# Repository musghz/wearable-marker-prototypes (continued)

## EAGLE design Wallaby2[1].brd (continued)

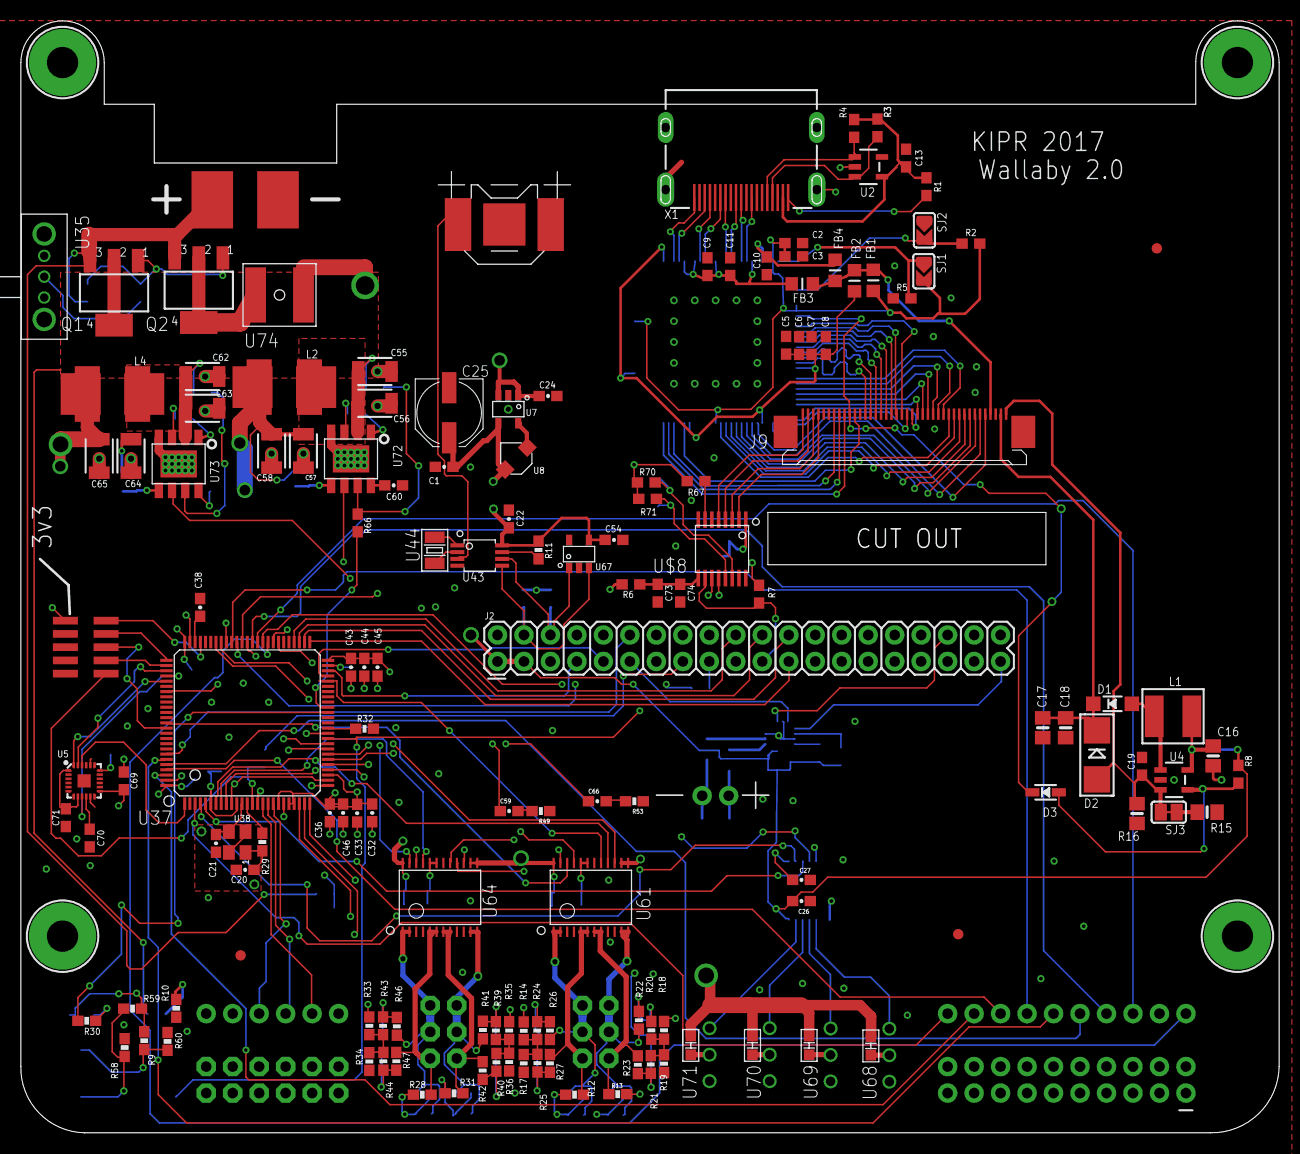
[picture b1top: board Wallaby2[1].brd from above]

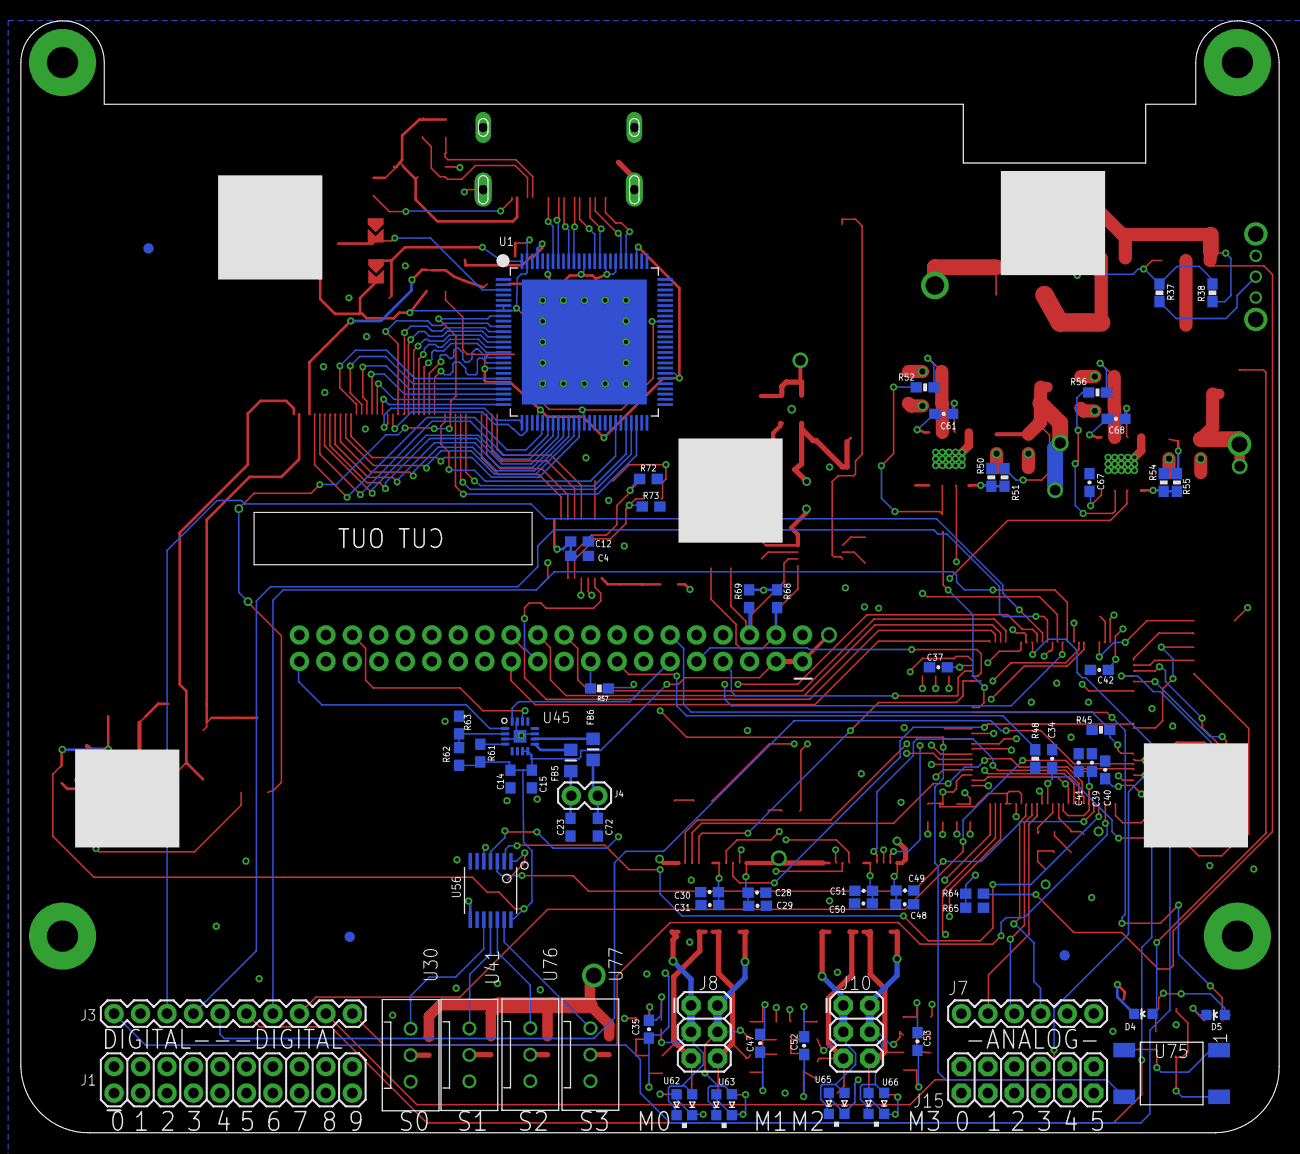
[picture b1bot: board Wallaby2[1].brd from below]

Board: 6 copper layers, 120.7 x 106.7 mm, 222 parts (73 on the bottom side), 199 nets.

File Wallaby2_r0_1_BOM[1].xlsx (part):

Item # | Qty | Ref Des | Manufacturer | Mfg Part # | Dist Part # | Distributor | Description | Package | Type
1 | 1 | J4 |  |  |  |  | Holes for speaker wire | 1X02 | DNS
2 | 1 | J3 | Harwin | M20-7821042 | 855-M20-7821042 | mouser | 1x10 female header | J3 | Thru-hole
3 | 1 | J1 | Harwin | M20-7831046 | 855-M20-7831046 | mouser | 2x10 female header | 2X10 | Thru-hole
4 | 1 | J7 | Harwin | M20-7820642 | 855-M20-7820642 | mouser | 1x6 female header | 1X06 | Thru-hole
5 | 2 | SJ1, SJ2 |  |  |  |  |  | SOLDERJUMPER_ARROW_NOPASTE | DNS
6 | 1 | U35 | C&K | 0S102011MA1QN1 | 611-OS102011MA1QN1 | mouser |  | OS-SPDT-MINI-SLIDE_SWITCH | Thru-hole
7 | 1 | SJ3 |  |  |  |  | -25mA | SOLDERJUMPER_CLOSEDWIRE | DNS
8 | 6 | R48,R66, R70, R71, R72, R73 | Yageo | RC0603JR-070RL | 603-RC0603JR-070RL | mouser | 0 ohm 0603 | 0603 | smt
8 | 2 | R6, R67 | Yageo | RC0603JR-070RL | 603-RC0603JR-070RL | mouser | 0 ohm 0603 | 0603 | DNS
9 | 33 | C2, C3,C4,C5,C6,C7,C8, C9, C10, C11, C13,C15,C19,C22, C26, C27, C28, C31, C32, 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 | Murata | GRM188R61E104KA01D | 81-GRM188R61E104KA1D | mouser | 0.1uF 20V | 0603-CAP | smt
9 | 1 | C74 | Murata | GRM188R61E104KA01D | 81-GRM188R61E104KA1D | mouser | 0.1uF 20V | 0603-CAP | DNS
10 | 4 | R38, R52, R56,R64 | Yageo | RC0603FR-10100KL | 603-RC0603FR-10100KL | mouser | 100k 1% | 0603-RES | smt
12 | 13 | R1, R2, R3, R4, R5, R8,R11, R32, R45, R50, R54, R58, R65 | Yageo | RC0603FR-0710KL | 603-RC0603FR-0710KL | mouser | 10k 1% | 0603-RES | smt
13 | 2 | R49, R53 | Yageo | RC0603FR-0710K5L | 603-RC0603FR-0710K5L | mouser | 10k5 1% | 0603-RES | smt
14 | 2 | C61, C68 | Murata | GRM188R71E103KA01D | 81-GRM39X103K25 | mouser | 10nF 25V | 0603-CAP | smt
15 | 1 | C71 | Murata | GRM1885C1H100JA01D | 81-GRM39C100D50 | mouser | 10pF 50v | 0603 | smt
16 | 1 | C16 | Murata | GRM21BR61E106KA73L | 81-GRM21BR61E106KA3L | mouser | 10uF 20V 20% | 0805-NO | smt
17 | 6 | C1,C14,C29, C30, C49, C50 | Murata | GRM188R61E106MA73J | 81-GRM188R61E106MA3J | mouser | 10uF 20V | 0603-CAP | smt
18 | 2 | R15, R16 | Yageo | RC0805FR-0712RL | 603-RC0805FR-0712RL | mouser | 12 ohm 1% 0805 | 0805-NO | smt
19 | 1 | L1 | Taiyo Yuden | NRS5040T150MMGJV | 963-NRS5040T150MMGJV | mouser | 15uH | INDUCTOR_5X5MM_NR5040_NOTHERMALS | smt
20 | 8 | R9, R10, R12, R13, R28, R30, R31, R57 | Yageo | RC0603FR-071KL | 603-RC0603FR-071KL | mouser | 1K ohm 1% | 0603-RES | smt
21 | 1 | R61 | Yageo | RC0603FR-071ML | 603-RC0603FR-071ML | mouser | 1M ohm 1% | 603 | smt
22 | 1 | D3 | Fairchild | 1N4148WS | 512-1N4148WS | mouser | 1N4148 | SOD-323 | smt
23 | 2 | C33, C36 | Murata | GRM188R71E105KA12D | 81-GRM188R71E105KA2D | mouser | 1uF | 0603-CAP | smt
24 | 2 | C17, C18 | Murata | GRM21BR71H105KA12L | 81-GRM21BR71H105KA2L | mouser | 1uF 50V 10% | 0805-NO | smt
25 | 3 | C37, C38,C12 | Murata | GRM188R61E225KA12D | 81-GRM188R61E225KA2D | mouser | 2.2uF | 0603-CAP | smt
25 | 1 | C73 | Murata | GRM188R61E225KA12D | 81-GRM188R61E225KA2D | mouser | 2.2uF | 0603-CAP | DNS
26 | 1 | U8 | Sumida | CDRH2D14NP-2R2NC | 851-CDRH2D14NP-2R2NC | mouser | 2.2uH | 3P2MM-X-3P2MM-INDUCTOR | smt
27 | 8 | C23, C72, C20, C21, C35, C47, C52, C53 | Murata | GRM1885C1H220JA01D | 81-GRM39C220J50 | mouser | 22pF | 0603 | smt
28 | 6 | C55, C56, C57, C62, C63, C64 | AVX | 1210YD226KAT2A | 581-1210YD226K | mouser | 22uF 16V | 1210@1 | smt
29 | 1 | R29 | Yageo | RC0603FR-07240RL | 603-RC0603FR-07240RL | mouser | 240R | 0603-RES | smt
30 | 1 | U2 | Microchip | 24LC02BT-I/OT | 579-24LC02BT-I/OT | mouser | 24LC02BT-I/OT | SOT23-5 | smt
31 | 1 | U74 | Littelfuse Inc. | 2920L500/16MR | 576-2920L500/16MR | mouser | 2920L500-16MR 16V 5A Poly Fuse | FUSE-2920 | smt
32 | 1 | J15 | Harwin | M20-7830646 | 855-M20-7830646 | mouser | 2X6 FEMALE | 2X6 | Thru-hole
33 | 8 | R20, R21, R24, R25, R39, R40, R43, R44 | Yageo | RC0603FR-072K2L | 603-RC0603FR-072K2L | mouser | 2k2 1% | 0603-RES | smt
34 | 1 | C25 | Panasonic | EEE-FTC331XAP | 667-EEE-FTC331XAP | mouser | 330uF 16V Electrolytic Cap | PANASONIC_D | smt
35 | 1 | R37 | Yageo | RC0603FR-073K3L | 603-RC0603FR-073K3L | mouser | 3K3 1% | 0603-RES | smt
36 | 2 | C24, C39 | Murata | GRM188R61E475KE11D | 81-GRM188R61E475KE1D | mouser | 4.7uF | 0603-CAP | smt
37 | 1 | J9 | TE Connectivity | 4-1734839-0 | 571-4-1734839-0 | mouser | Touchscreen Connector 40 Pin | 4-1734839-0 | smt
38 | 8 | R14, R17, R18, R19, R33, R34, R35, R36 | Yageo | RC0603FR-07470RL | 603-RC0603FR-07470RL | mouser | 470R 1% | 0603-RES | smt
39 | 1 | X1 | Molex | 47151-0001 | 538-47151-0001 | mouser | 47151-0001 | HDMI_MOLEX_47151-0001_DIMLAYER | smt, thru-hole posts
40 | 1 | R7 | Yageo | RC0603FR-0747KL | 603-RC0603FR-0747KL | mouser | 47k 1% | 0603 | smt
41 | 2 | C58, C65 | Murata | GRM32ER61C476KE15K | 81-GRM32ER61C476KE5K | mouser | 47uF | 1210@1 | smt
42 | 1 | R55 | Yageo | RC0603FR-0752K3L | 603-RC0603FR-0752K3L | mouser | 52k3 1% | 0603-RES | smt
43 | 2 | L2,L4 | Vishay | IHLP3232CZER6R8M01 | 70-IHLP3232CZER6R8M0 | mouser | 6.5uH | INDUCT-3232-1050 | smt
44 | 1 | R51 | Yageo | RC0603FR-0764K9L | 603-RC0603FR-0764K9L | mouser | 64k9 1% | 0603-RES | smt
45 | 8 | R22, R23, R26, R27, R41, R42, R46, R47 | Yageo | RC0603FR-076K8L | 603-RC0603FR-076K8L | mouser | 6k8 1% | 0603-RES | smt
46 | 2 | C59, C66 | Murata | GRM188R71H682JA01D | 81-GRM188R71H682JA | mouser | 6p8nF | 0603-CAP | smt
47 | 1 | U5 | InvenSense | MPU-9250 | 1428-1019-1-ND | digikey | 9DoF IMU | QFN24-3X3 | smt
48 | 1 | U$8 | Texas Instruments | TSC2007IPWR | 595-TSC2007IPWR | mouser | TSC2007 | TSSOP16 | smt
49 | 2 | U72, U73 | Diodes Incorporated | AP65502SP-13 | 621-AP65502SP-13 | mouser | AP65502 | SO-8EP | smt
50 | 4 | U62, U63, U65, U66 | Kingbright | APB3025ESGC-F01 | 604-APB3025ESGC-F01 | mouser | APB3025ESGC-F01 | DUAL_SMT_LED | smt
51 | 1 | U67 | Microchip | AT24CS01-STUM-T | 556-AT24CS01-STUM-T | mouser | AT24CS01-STUM-T | SOT-23-5 | smt
52 | 2 | Q1, Q2 | Fairchild | 512-FDT434P | FDT434P | mouser | P-CH 20V FET | SOT223 | smt
53 | 1 | U42 | Keystone | 2998TR | 534-2998TR | mouser | COINCELL_6P8MM | COIN_CELL_HOLDER_6P8MM | smt
54 | 4 | U30, U41, U76, U77 | TE Connectivity | 5-103414-1 | 571-5-103414-1 | mouser | CONN-HEADER-5-103414-1 | HEADER-5-103414-1 | Thru-hole
55 | 1 | J2 | Adafruit | 1992 |  | adafruit | 2x20 tall female Pi connector | 2X20 | Thru-hole
56 | 1 | U39 | Harwin | M50-3600542 | 855-M50-3600542 |  | CORTEX_JTAG | CORTEX-JTAG-HDR | Thru-hole
57 | 1 | U44 | ECS | ECS-.327-12.5-34B-TR | 520-327-12.5-34B | mouser | CRYSTAL-ECS-ECX34B 32.768KHz | CRYSTAL-ECX34B-3P2MM_1P5MM | smt
58 | 2 | R62, R63 |  |  |  |  | DNP | 0603 | smt
59 | 2 | R59, R60 |  |  |  |  | DNP | 0603-RES | smt
60 | 1 | U43 | Maxim Integrated | DS1340U-33+ | 700-DS1340U-33 | mouser | DS1340U | USOP-8 | smt
61 | 1 | U4 | Fairchild | FAN5333BSX | 512-FAN5333BSX | mouser | FAN5333BSX | SOT23-5 | smt
62 | 2 | J8, J10 | Harwin | M20-7830342 | 855-M20-7830342 | mouser | FEMALE 2x3 | 2X3 | Thru-hole
63 | 4 | U68, U69, U70, U71 | Littelfuse Inc. | 0603L100SLYR | 576-0603L100SLYR | mouser | FUSE-RESET-0603L100SLYR | 0603 | smt
64 | 6 | FB1, FB2, FB3, FB4, FB5, FB6 | Murata | BLM21AG601SN1D | 81-BLM21A601F | mouser | Ferrite | _0805MP | smt
65 | 1 | U7 | Texas Instruments | LM3671MF-3.3/NOPB | 926-LM3671MF-3.3NOPB | mouser | LM3671 | SOT-23-5 | smt
66 | 1 | U45 | Maxim Integrated | MAX98357AETE+T | 700-MAX98357AETE+T | mouser | MAX98357 audio amp | TQFN-16 | smt
67 | 1 | D1 | Fairchild | MBR0540 | 512-MBR0540 | mouser | MBR0540 | SOD-123 | smt
68 | 1 | D2 | OM Semiconductor | 1SMB5934BT3G | 863-1SMB5934BT3G | mouser | 24V 3W Zener | SMADIODE | smt
69 | 4 | U31, U32, U33, U34 |  |  |  |  | MOUNTINGHOLE3.0 | MOUNTINGHOLE_3.0_PLATED | DNS
70 | 1 | U75 | TE Connectivity | 1571527-2 | 506-1571527-2 | mouser | PUSHBUTTON-1571527-2 | BUTTON-1571527-2 | smt
71 | 1 | U37 | STMicroelectronics | STM32F427VIT6 | 511-STM32F427VIT6 | mouser | STM32F427VIT6 | LQFP-100 | smt
72 | 2 | U61, U64 | Toshiba | TB6612FNG,C,8,EL | 757-TB6612FNGC8EL | mouser | TB6612FNG | SSOP24 | smt
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
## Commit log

2017-01-23 E:\My_Documents\MS_PhD\OpenSCAD
